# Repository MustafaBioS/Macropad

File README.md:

# Macropad
Macropad is a hardware project that allows you to bind keys to do certain tasks on your PC

# Why
Because it's a cool project and its also very usefuL!

# Components
This project uses the following:
- SEEDUINO-XIAO MCU
- 4 Tactile Switches
- Rotary Encoder Switch
- 128x32 OLED Display

# Schematic, PCB, 3D Model, and Zine!

## Schematic

## PCB

## 3D Model

## Zine

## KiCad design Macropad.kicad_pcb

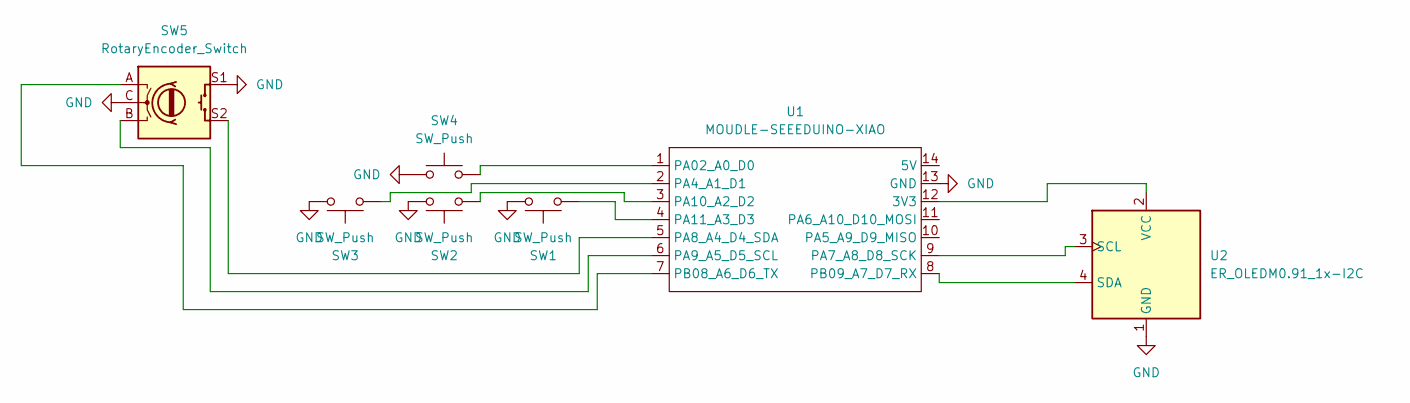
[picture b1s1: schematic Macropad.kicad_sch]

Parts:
SW1, SW2, SW3, SW4: SW_Push; SW_Cherry_MX_1.50u_PCB
SW5: RotaryEncoder_Switch; RotaryEncoder_Alps_EC11E-Switch_Vertical_H20mm
U1: MOUDLE-SEEEDUINO-XIAO; XIAO-Generic-Hybrid-14P-2.54-21X17.8MM
U2: ER_OLEDM0.91_1x-I2C

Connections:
GND: SW1.2, SW2.2, SW3.2, SW4.1, SW5.C, SW5.S1, U1.13 (GND), U2.1 (GND)
unnamed: U1.12 (3V3), U2.2 (VCC)
unnamed: SW4.2, U1.1 (PA02_A0_D0)
unnamed: SW3.1, U1.2 (PA4_A1_D1)
unnamed: U1.9 (PA7_A8_D8_SCK), U2.3 (SCL)
unnamed: SW5.S2, U1.5 (PA8_A4_D4_SDA)
unnamed: SW5.B, U1.6 (PA9_A5_D5_SCL)
unnamed: SW2.1, U1.3 (PA10_A2_D2)
unnamed: SW1.1, U1.4 (PA11_A3_D3)
unnamed: SW5.A, U1.7 (PB08_A6_D6_TX)
unnamed: U1.8 (PB09_A7_D7_RX), U2.4 (SDA)

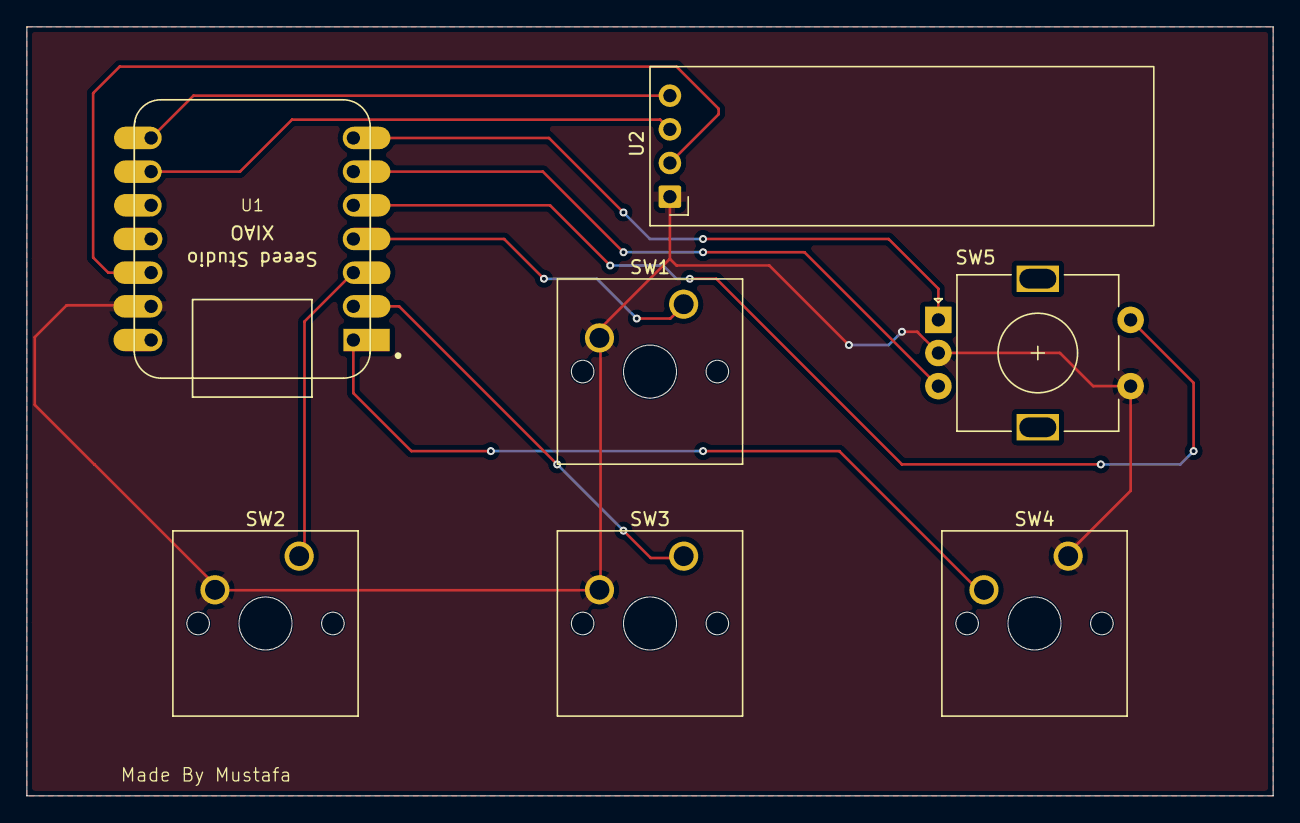
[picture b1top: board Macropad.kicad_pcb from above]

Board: 2 copper layers, 94.0 x 58.0 mm, 7 parts (0 on the bottom side), 11 nets.

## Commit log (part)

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2026-06-10 Rename Macropad.ino to firmware/Macropad.ino
2026-06-10 Rename BOM.csv to docs/BOM.csv
2026-06-10 Rename README.md to docs/README.md
2026-06-10 Rename Macropad.kicad_pcb to pcb/Macropad.kicad_pcb
2026-06-10 Rename Macropad.kicad_pro to pcb/Macropad.kicad_pro
2026-06-10 Rename Macropad.kicad_sch to pcb/Macropad.kicad_sch
2026-06-10 Rename Macropad.f3d to 3d/Macropad.f3d
2026-06-10 Rename Macropad.f3d to Macropad.f3d
2026-06-10 Rename Macropad.step to model/Macropad.step
2026-06-11 Rename A5 - 1 (6).png to Macropad-Zine.png
2026-06-11 Rename A5 - 1 (2).pdf to Zine
2026-06-11 Rename Zine to Zine.pdf
2026-06-15 Rename Gerber.zip to pcb/Gerber.zip
2026-06-30 Rename JOURNAL (2).md to JOURNAL.md
